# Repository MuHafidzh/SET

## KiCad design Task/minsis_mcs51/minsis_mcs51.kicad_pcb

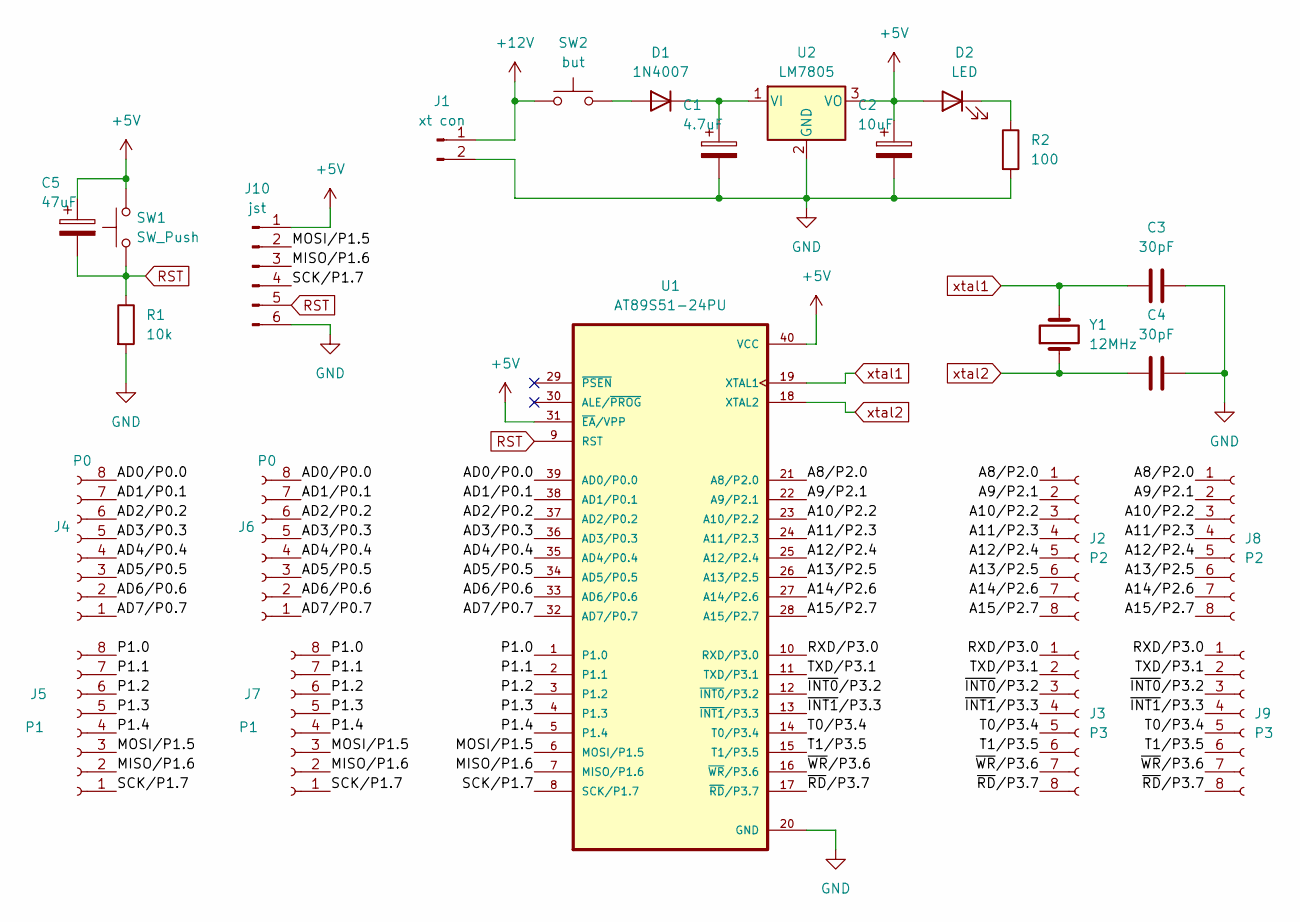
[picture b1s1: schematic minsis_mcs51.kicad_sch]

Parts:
C1: 4.7uF; CP_Radial_D4.0mm_P2.00mm
C2: 10uF; CP_Radial_D4.0mm_P2.00mm
C3, C4: 30pF; C_Rect_L4.6mm_W2.0mm_P2.50mm_MKS02_FKP02
C5: 47uF; CP_Radial_D4.0mm_P2.00mm
D1: 1N4007; D_DO-41_SOD81_P10.16mm_Horizontal
D2: LED; LED_D5.0mm
J1: xt con; TerminalBlock_Phoenix_MKDS-1,5-2_1x02_P5.00mm_Horizontal
J2, J8: P2; PinHeader_1x08_P2.54mm_Vertical
J3, J9: P3; PinHeader_1x08_P2.54mm_Vertical
J4, J6: P0; PinHeader_1x08_P2.54mm_Vertical
J5, J7: P1; PinHeader_1x08_P2.54mm_Vertical
J10: jst; JST_XH_B6B-XH-A_1x06_P2.50mm_Vertical
R1: 10k; R_Axial_DIN0204_L3.6mm_D1.6mm_P7.62mm_Horizontal
R2: 100; R_Axial_DIN0204_L3.6mm_D1.6mm_P7.62mm_Horizontal
SW1: SW_Push; SW_DIP_SPSTx01_Slide_6.7x4.1mm_W7.62mm_P2.54mm_LowProfile
SW2: but; TerminalBlock_Phoenix_MKDS-1,5-2_1x02_P5.00mm_Horizontal
U1: AT89S51-24PU; DIP-40_W15.24mm_Socket_LongPads; PARTREV B
U2: LM7805; TO-220-3_Vertical
Y1: 12MHz; Resonator-2Pin_W8.0mm_H3.5mm

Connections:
+5V: C2.1, C5.1, D2.2 (A), J10.1, SW1.2, U1.31 (~EA/VPP), U1.40 (VCC), U2.3 (VO)
+12V: J1.1, SW2.1
/A8/P2.0: J2.1, J8.1, U1.21 (A8/P2.0)
/A9/P2.1: J2.2, J8.2, U1.22 (A9/P2.1)
/A10/P2.2: J2.3, J8.3, U1.23 (A10/P2.2)
/A11/P2.3: J2.4, J8.4, U1.24 (A11/P2.3)
/A12/P2.4: J2.5, J8.5, U1.25 (A12/P2.4)
/A13/P2.5: J2.6, J8.6, U1.26 (A13/P2.5)
/A14/P2.6: J2.7, J8.7, U1.27 (A14/P2.6)
/A15/P2.7: J2.8, J8.8, U1.28 (A15/P2.7)
/AD0/P0.0: J4.8, J6.8, U1.39 (AD0/P0.0)
/AD1/P0.1: J4.7, J6.7, U1.38 (AD1/P0.1)
/AD2/P0.2: J4.6, J6.6, U1.37 (AD2/P0.2)
/AD3/P0.3: J4.5, J6.5, U1.36 (AD3/P0.3)
/AD4/P0.4: J4.4, J6.4, U1.35 (AD4/P0.4)
/AD5/P0.5: J4.3, J6.3, U1.34 (AD5/P0.5)
/AD6/P0.6: J4.2, J6.2, U1.33 (AD6/P0.6)
/AD7/P0.7: J4.1, J6.1, U1.32 (AD7/P0.7)
/MISO/P1.6: J5.2, J7.2, J10.3, U1.7 (MISO/P1.6)
/MOSI/P1.5: J5.3, J7.3, J10.2, U1.6 (MOSI/P1.5)
/P1.0: J5.8, J7.8, U1.1 (P1.0)
/P1.1: J5.7, J7.7, U1.2 (P1.1)
/P1.2: J5.6, J7.6, U1.3 (P1.2)
/P1.3: J5.5, J7.5, U1.4 (P1.3)
/P1.4: J5.4, J7.4, U1.5 (P1.4)
/RXD/P3.0: J3.1, J9.1, U1.10 (RXD/P3.0)
/SCK/P1.7: J5.1, J7.1, J10.4, U1.8 (SCK/P1.7)
/T0/P3.4: J3.5, J9.5, U1.14 (T0/P3.4)
/T1/P3.5: J3.6, J9.6, U1.15 (T1/P3.5)
/TXD/P3.1: J3.2, J9.2, U1.11 (TXD/P3.1)
/~INT0/P3.2: J3.3, J9.3, U1.12 (~INT0/P3.2)
/~INT1/P3.3: J3.4, J9.4, U1.13 (~INT1/P3.3)
/~RD/P3.7: J3.8, J9.8, U1.17 (~RD/P3.7)
/~WR/P3.6: J3.7, J9.7, U1.16 (~WR/P3.6)
GND: C1.2, C2.2, C3.2, C4.1, J1.2, J10.6, R1.2, R2.2, U1.20 (GND), U2.2 (GND)
unnamed: D1.2 (A), SW2.2
unnamed: C1.1, D1.1 (K), U2.1 (VI)
unnamed: D2.1 (K), R2.1
RST: C5.2, J10.5, R1.1, SW1.1, U1.9 (RST)
xtal1: C3.1, U1.19 (XTAL1), Y1.2
xtal2: C4.2, U1.18 (XTAL2), Y1.1

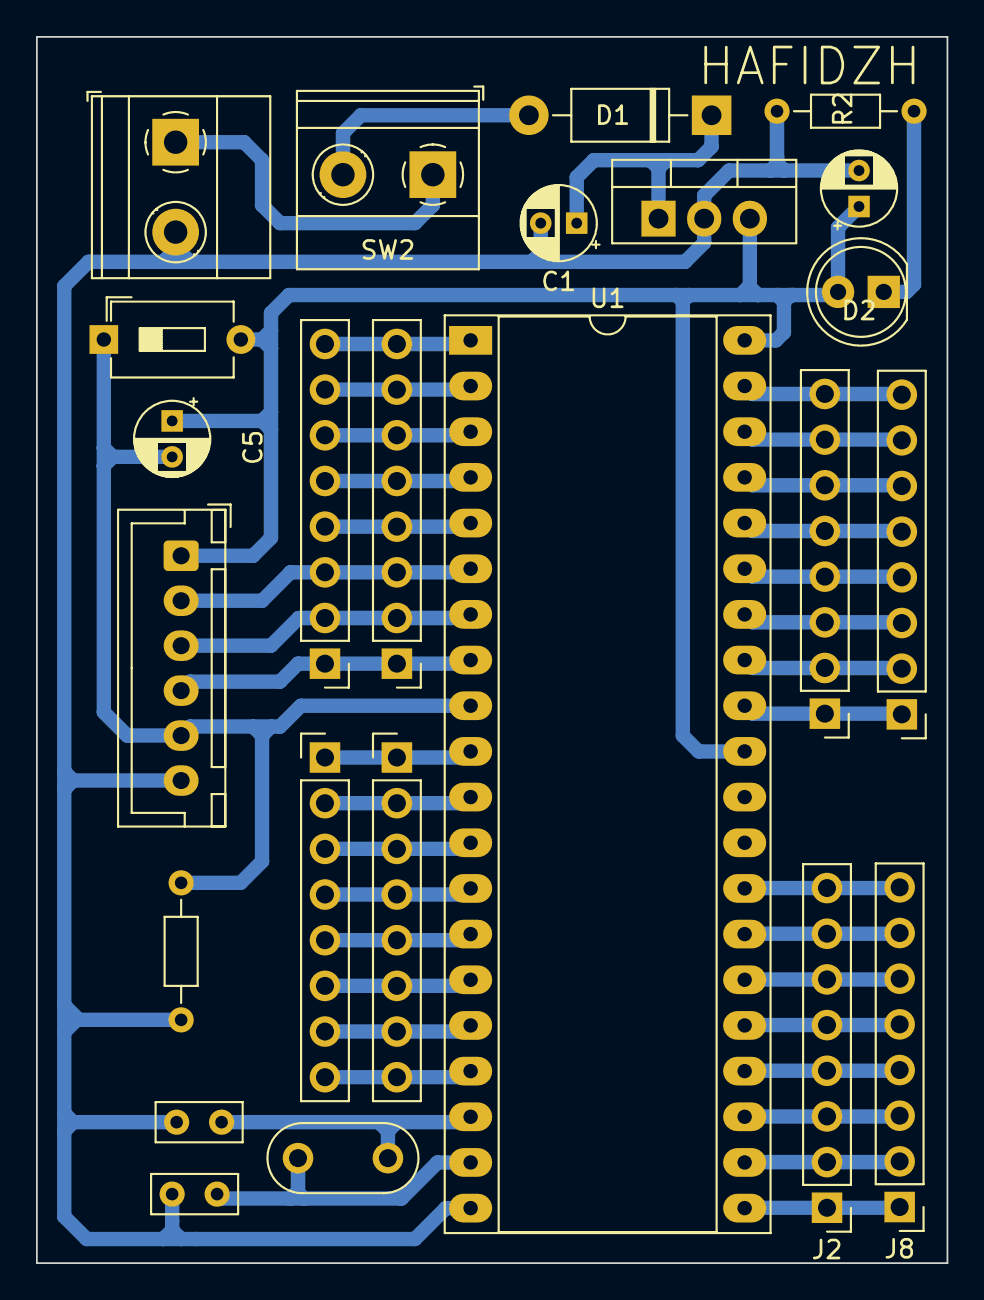
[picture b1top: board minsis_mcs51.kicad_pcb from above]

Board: 2 copper layers, 50.6 x 68.2 mm, 24 parts (0 on the bottom side), 41 nets.

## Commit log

2025-02-03 FP SET
2025-02-03 SET Tasks
